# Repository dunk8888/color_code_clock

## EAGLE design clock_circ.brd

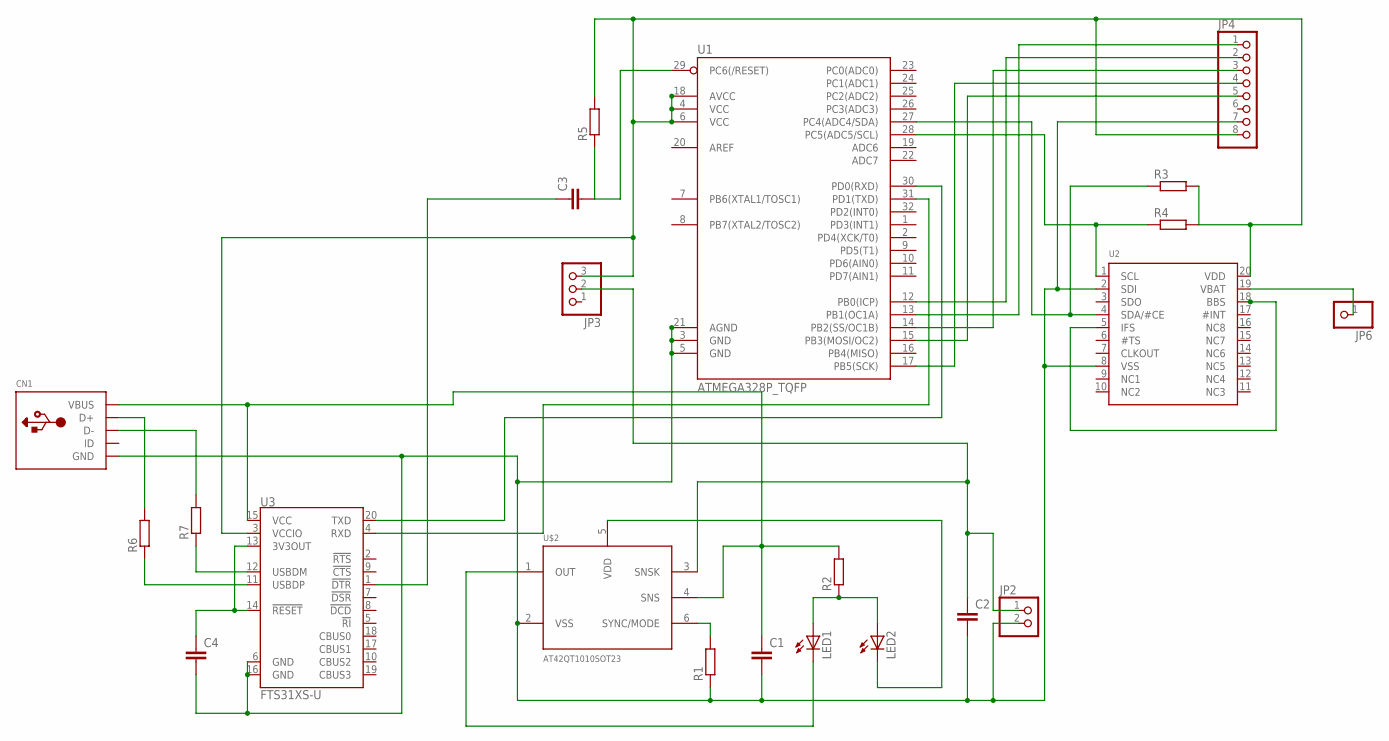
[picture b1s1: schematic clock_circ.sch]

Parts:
C1, C2, C4: CC1005; C1005
C3: CC0603; C0603
CN1: USBMINIB; USB-MINIB
JP2: PINHD-1X2; 1X02
JP3: PINHD-1X3; 1X03
JP4: HEADER-1X8; 1X08_OVAL
JP6: PINHD-1X1; 1X01
LED1, LED2: LED_E; LED_1206
R1, R2, R3, R4, R5, R6, R7: RR0603; R0603
U1: ATMEGA328P_TQFP; TQFP32-08
U2: RTC_PCF2129A; SOIC20WIDE
U3: FTS31XS-U; SSOP20_L
U$2: AT42QT1010SOT23; SOT23-6

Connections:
unnamed: LED1.A, LED2.A, R2.1
unnamed: LED1.C, U$2.1 (OUT)
unnamed: LED2.C, U$2.5 (VDD)
unnamed: JP3.3, JP4.8, R3.2, R4.2, R5.2, U1.4 (VCC), U1.6 (VCC), U1.18 (AVCC), U2.20 (VDD), U3.3 (VCCIO)
unnamed: JP4.1, U1.13 (PB1(OC1A))
unnamed: R1.2, U$2.6 (SYNC/MODE)
unnamed: JP6.1, U2.19 (VBAT)
unnamed: C2.1, JP2.1, JP3.2, U$2.3 (SNSK)
unnamed: R4.1, U1.28 (PC5(ADC5/SCL)), U2.1 (SCL)
unnamed: R3.1, U1.27 (PC4(ADC4/SDA)), U2.4 (SDA/#CE)
unnamed: JP4.5, U1.15 (PB3(MOSI/OC2))
unnamed: U2.5 (IFS), U2.18 (BBS)
unnamed: C1.1, CN1.VBUS, R2.2, U3.15 (VCC), U$2.4 (SNS)
unnamed: JP4.4, U1.17 (PB5(SCK))
unnamed: CN1.D+, R6.2
unnamed: C3.1, U3.1 (!DTR)
unnamed: C3.2, R5.1, U1.29 (PC6(/RESET))
unnamed: U1.31 (PD1(TXD)), U3.4 (RXD)
unnamed: U1.30 (PD0(RXD)), U3.20 (TXD)
unnamed: C4.1, U3.13 (3V3OUT), U3.14 (!RESET)
unnamed: JP4.2, U1.12 (PB0(ICP))
unnamed: JP4.3, U1.14 (PB2(SS/OC1B))
unnamed: CN1.D-, R7.2
unnamed: R7.1, U3.12 (USBDM)
unnamed: R6.1, U3.11 (USBDP)
unnamed: C1.2, C2.2, C4.2, CN1.GND, JP2.2, JP4.7, R1.1, U1.3 (GND), U1.5 (GND), U1.21 (AGND), U2.2 (SDI), U2.8 (VSS), U3.6 (GND), U3.16 (GND), U$2.2 (VSS)

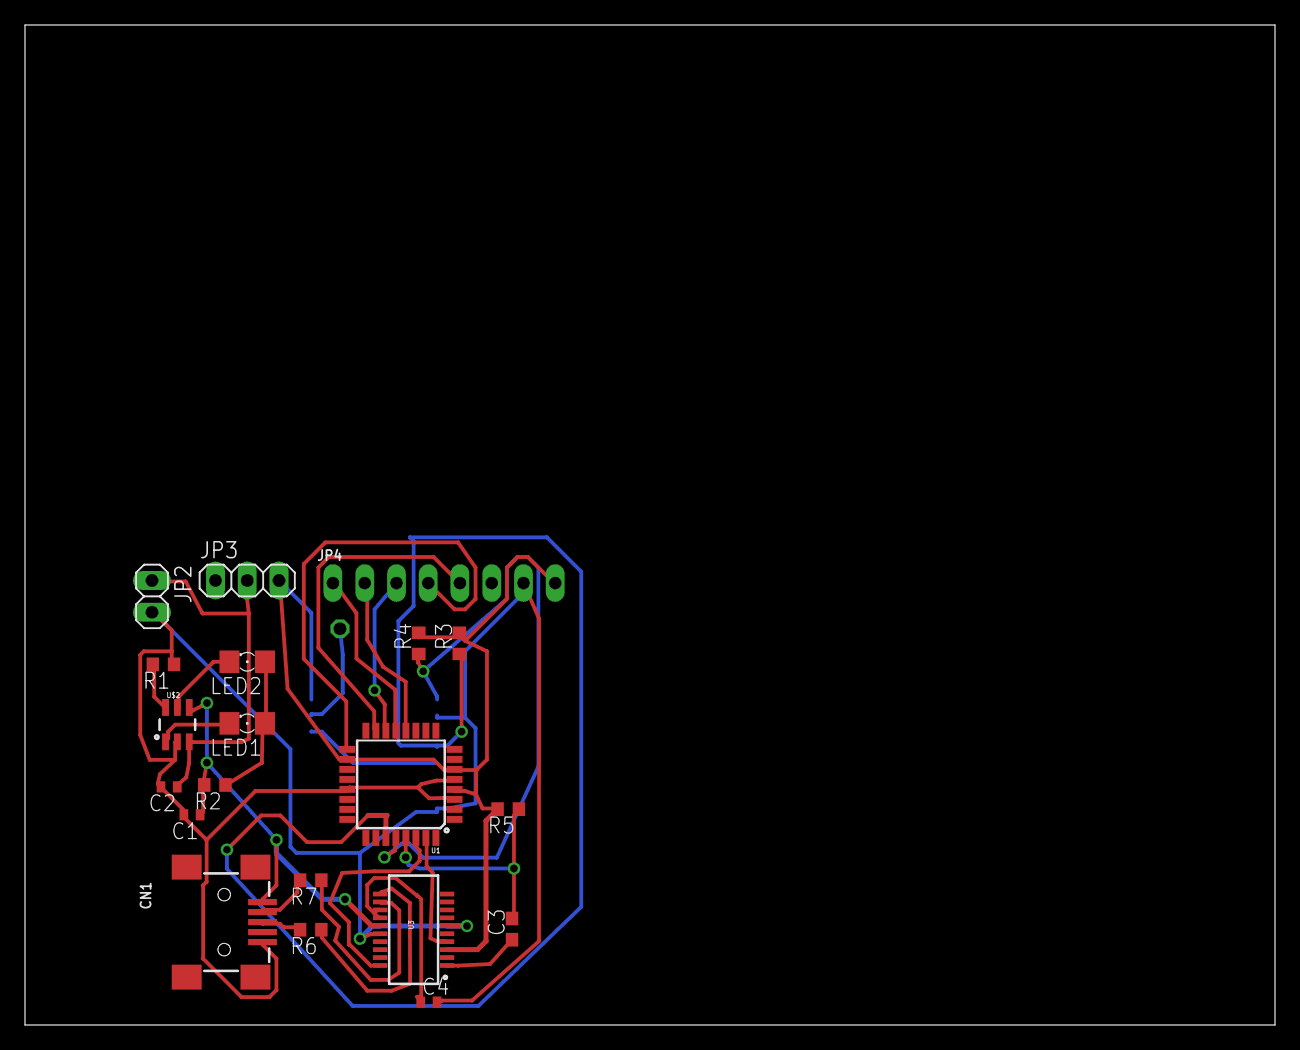
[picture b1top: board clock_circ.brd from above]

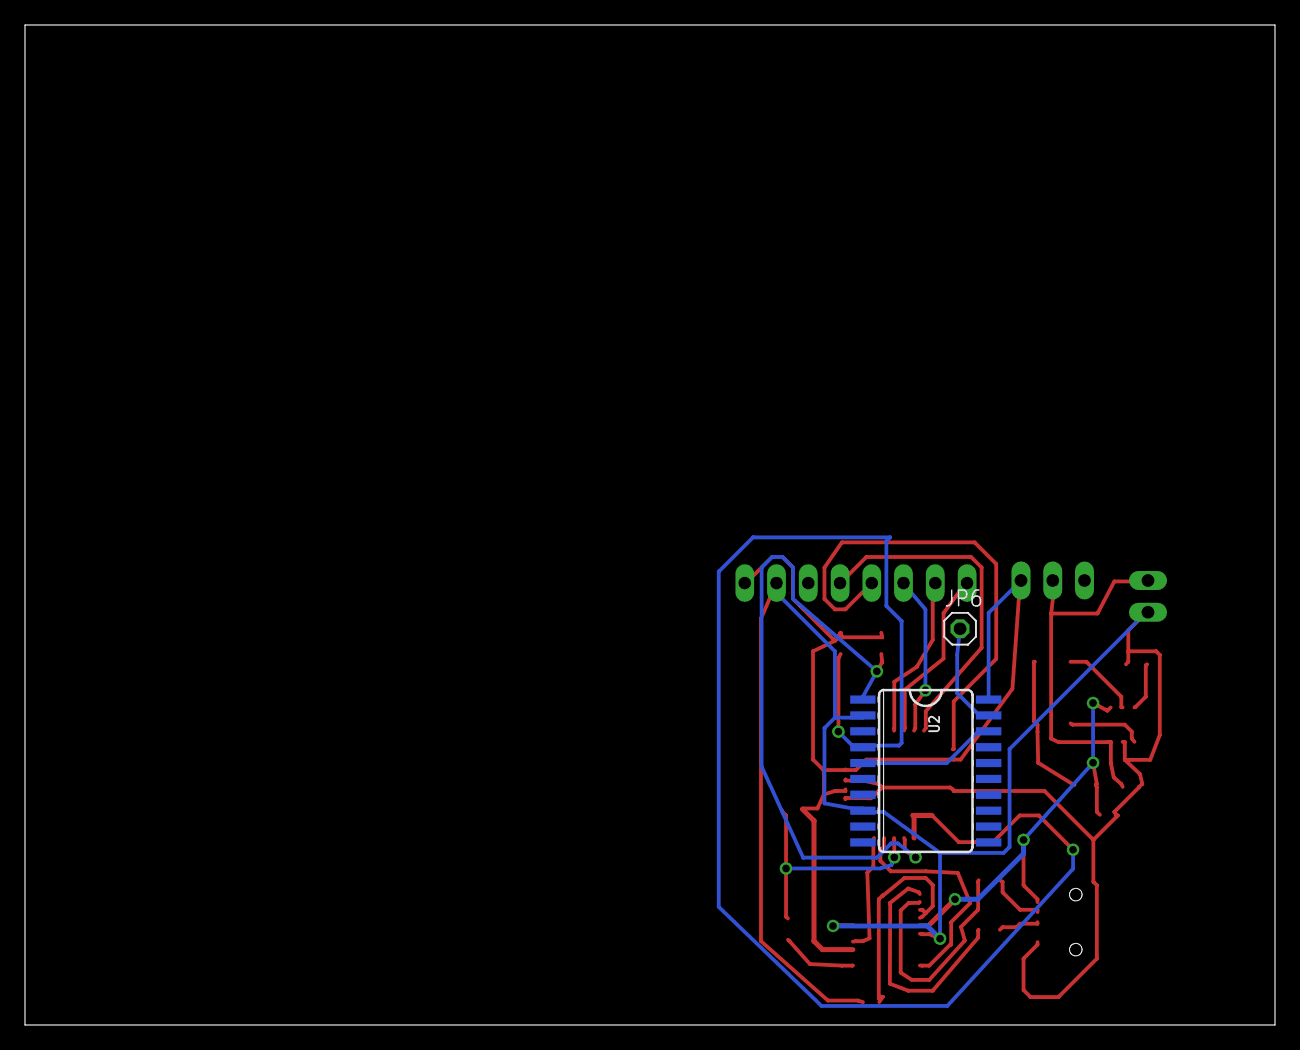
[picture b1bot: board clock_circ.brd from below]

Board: 2 copper layers, 100.0 x 80.0 mm, 22 parts (2 on the bottom side), 26 nets.

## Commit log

2015-10-24 initial submission
2015-10-31 Halloween clock!

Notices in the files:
parts and their libraries:
SparkFun-DigitalIC: Licensing: Creative Commons ShareAlike 4.0 International - https://creativecommons.org/licenses/by-sa/4.0
microbuilder: This work is placed in the public domain, and may be freely used for commercial and non-commercial work with the following conditions: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
